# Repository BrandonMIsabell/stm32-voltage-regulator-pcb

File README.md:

# stm32-voltage-regulator-pcb
Routed a custom 5V linear regulator PCB in KiCad to power an STM32 Nucleo board, utilizing an LM358 op-amp and IRFZ44N MOSFET for closed-loop feedback control  Fabricated physical hardware from custom Gerber/Drill files and designed a matching 3D-printed enclosure in Autodesk Fusion using exported STEP models

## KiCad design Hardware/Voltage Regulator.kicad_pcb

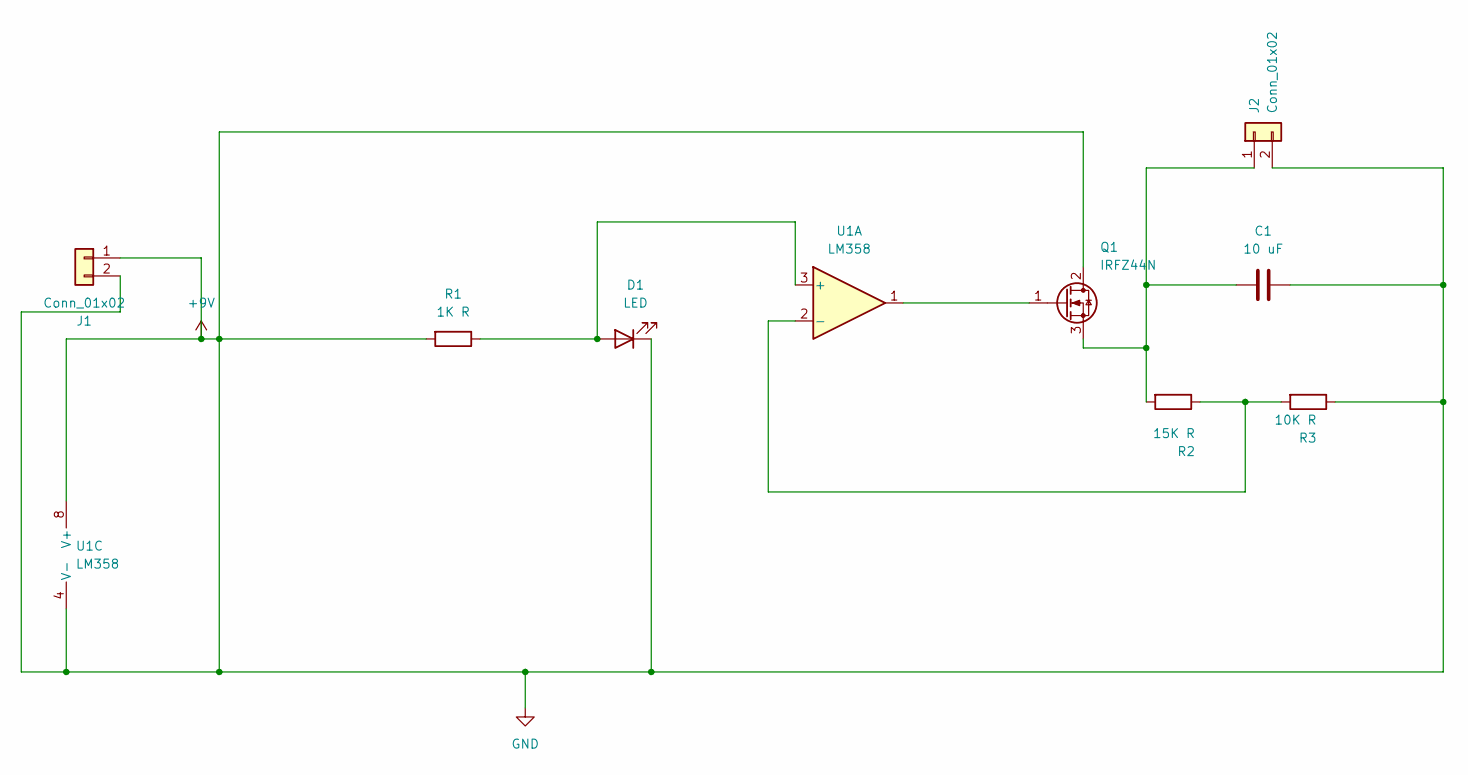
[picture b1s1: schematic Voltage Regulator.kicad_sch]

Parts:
C1: 10 uF; CP_Radial_D5.0mm_P2.00mm
D1: LED; LED_D5.0mm
J1, J2: Conn_01x02; PinHeader_1x02_P2.54mm_Vertical
Q1: IRFZ44N; TO-220-3_Vertical
R1: 1K R; R_Axial_DIN0207_L6.3mm_D2.5mm_P7.62mm_Horizontal
R2: 15K R; R_Axial_DIN0207_L6.3mm_D2.5mm_P7.62mm_Horizontal
R3: 10K R; R_Axial_DIN0207_L6.3mm_D2.5mm_P7.62mm_Horizontal
U1: LM358; DIP-8_W7.62mm

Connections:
+9V: C1.1, D1.1 (K), J1.1, J1.2, J2.2, Q1.2 (D), R1.2, R3.1, U1.4 (V-), U1.8 (V+)
unnamed: D1.2 (A), R1.1, U1.3 (+)
unnamed: C1.2, J2.1, Q1.3 (S), R2.2
unnamed: Q1.1 (G), U1.1
unnamed: R2.1, R3.2, U1.2 (-)

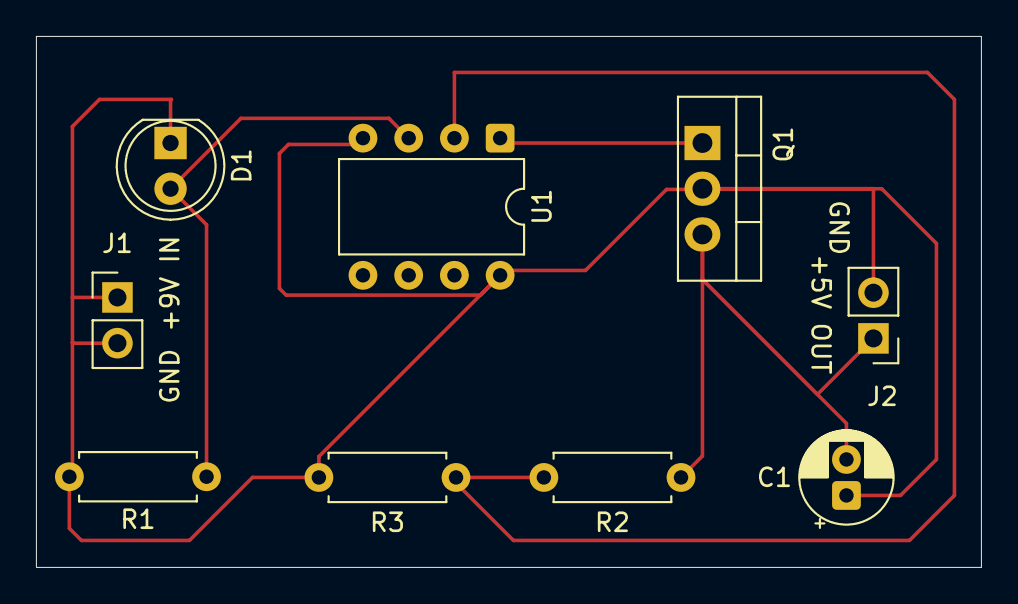
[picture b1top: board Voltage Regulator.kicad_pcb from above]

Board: 2 copper layers, 52.5 x 29.5 mm, 9 parts (0 on the bottom side), 5 nets.
